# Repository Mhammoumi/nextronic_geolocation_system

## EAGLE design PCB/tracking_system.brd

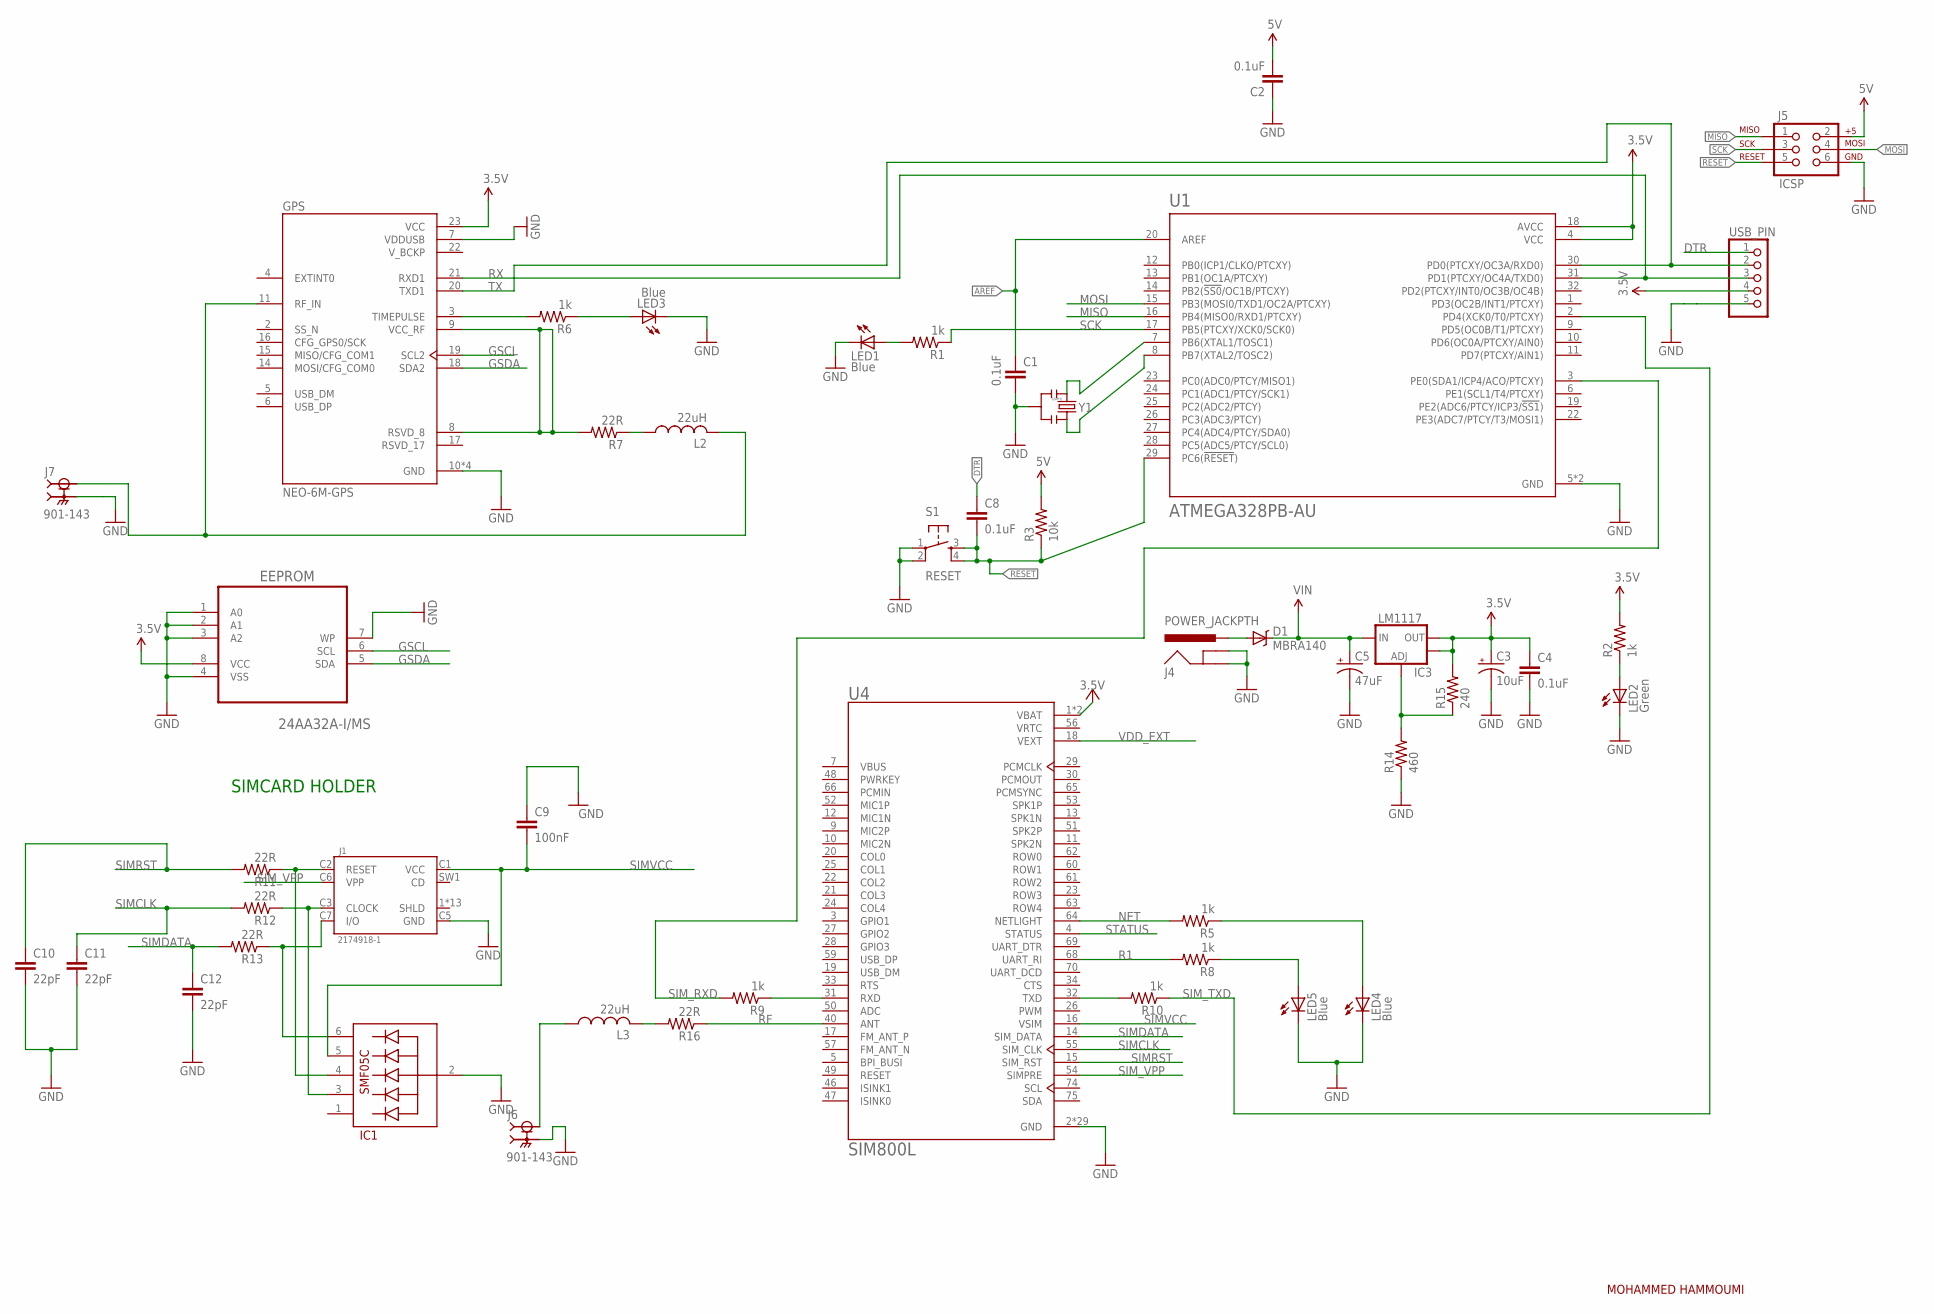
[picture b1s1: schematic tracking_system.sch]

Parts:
C1, C2, C4, C8: 0.1uF; 0603-CAP
C3: 10uF; EIA3216
C5: 47uF; PANASONIC_D; MPN EEE1CA470SP
C9: 100nF; 0603-CAP
C10, C11, C12: 22pF; 0603-CAP
D1: MBRA140; SMA-DIODE; MPN B140-13-F
EEPROM: 24AA32A-I/MS; SOP65P490X110-8N
GPS: NEO-6M-GPS; XCVR_NEO-6M-GPS
IC1: SMF05C; SC-70-6
IC3: LM1117; SOT223-ALT1; MPN LD1117S33TR
J1: 2174918-1; TE_2174918-1
J4: POWER_JACKPTH; POWER_JACK_PTH
J5: ICSP; 2X3
J6, J7: 901-143; AMPHENOL_901-143
L2, L3: 22uH; L3225P
LED1, LED3, LED4, LED5: Blue; LED-1206-NO_SILK
LED2: Green; LED-1206-NO_SILK
R1, R2, R5, R6, R8, R9, R10: 1k; 0603-RES
R3: 10k; 0603-RES
R7, R11, R12, R13, R16: 22R; 0603-RES
R14: 460; 0603-RES
R15: 240; 0603-RES
S1: RESET; TACTILE_SWITCH_SMD
U1: ATMEGA328PB-AU; QFP80P900X900X120-32N
U4: SIM800L; MODULE_SIM800L
USB_PIN: PINHD-1X5; 1X05
Y1: 16MHz; RESONATOR-SMD

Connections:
3.3V: EEPROM.8 (VCC), GPS.23 (VCC)
5V: C2.2, C3.A (+), C4.1, IC3.2 (OUT), IC3.4 (OUT), J5.2, R2.2, R3.2, R15.2, U1.4 (VCC), U1.18 (AVCC), USB_PIN.4
AREF: C1.1, U1.20 (AREF)
DTR: C8.1, USB_PIN.1
GND: C1.2, C2.1, C3.C (-), C4.2, C5.-, C9.1, C10.2, C11.2, C12.2, EEPROM.1 (A0), EEPROM.2 (A1), EEPROM.3 (A2), EEPROM.4 (VSS), EEPROM.7 (WP), GPS.7 (VDDUSB), GPS.10 (GND), GPS.12 (GND), GPS.13 (GND), GPS.24 (GND), IC1.2, J1.C5 (GND), J4.GND, J4.GNDBREAK, J5.6, J6.2, J6.3 (2), J6.4 (2), J6.5 (2), J7.2, J7.3 (2), J7.4 (2), J7.5 (2), LED1.C, LED2.C, LED3.C, LED4.C, LED5.C, R14.1, S1.1, S1.2, U1.5 (GND), U1.21 (GND), U4.2 (GND), U4.6 (GND), U4.8 (GND), U4.35 (GND), U4.37 (GND), U4.38 (GND), U4.39 (GND), U4.41 (GND), U4.43 (GND), U4.44 (GND), U4.45 (GND), U4.58 (GND), U4.67 (GND), U4.71 (GND), U4.72 (GND), U4.73 (GND), U4.76 (GND), U4.77 (GND), U4.78 (GND), U4.79 (GND), U4.80 (GND), U4.81 (GND), U4.82 (GND), U4.83 (GND), U4.84 (GND), U4.85 (GND), U4.86 (GND), U4.87 (GND), U4.88 (GND), USB_PIN.5, Y1.2
GSCL: EEPROM.6 (SCL), GPS.19 (SCL2)
GSDA: EEPROM.5 (SDA), GPS.18 (SDA2)
MISO: J5.1, U1.16 (PB4(MISO0/RXD1/PTCXY))
MOSI: J5.4, U1.15 (PB3(MOSI0/TXD1/OC2A/PTCXY))
unnamed: LED2.A, R2.1
unnamed: LED1.A, R1.2
unnamed: U1.7 (PB6(XTAL1/TOSC1)), Y1.1
unnamed: U1.8 (PB7(XTAL2/TOSC2)), Y1.3
unnamed: D1.A, J4.PWR
unnamed: GPS.3 (TIMEPULSE), R6.2
unnamed: LED3.A, R6.1
unnamed: GPS.8 (RSVD_8), GPS.9 (VCC_RF), R7.2
unnamed: L2.1, R7.1
unnamed: GPS.11 (RF_IN), J7.1, L2.2
unnamed: R9.1, U4.31 (RXD)
unnamed: R10.2, U4.32 (TXD)
unnamed: IC1.6, J1.C7 (I/O), R13.1
unnamed: LED5.A, R8.1
unnamed: IC3.1 (ADJ), R14.2, R15.1
unnamed: LED4.A, R5.1
unnamed: IC1.3, J1.C3 (CLOCK), R12.1
unnamed: IC1.4, J1.C2 (RESET), R11.1
unnamed: L3.2, R16.2
unnamed: J6.1, L3.1
NET: R5.2, U4.64 (NETLIGHT)
R1: R8.2, U4.68 (UART_RI)
RESET: C8.2, J5.5, R3.1, S1.3, S1.4, U1.29 (PC6(!RESET!))
RF: R16.1, U4.40 (ANT)
RX: GPS.21 (RXD1), U1.31 (PD1(PTCXY/OC4A/TXD0)), USB_PIN.3
SCK: J5.3, R1.1, U1.17 (PB5(PTCXY/XCK0/SCK0))
SHLD: J1.1 (SHLD), J1.2 (SHLD), J1.3 (SHLD), J1.4 (SHLD), J1.5 (SHLD), J1.6 (SHLD), J1.7 (SHLD), J1.8 (SHLD), J1.9 (SHLD), J1.10 (SHLD), J1.11 (SHLD), J1.12 (SHLD), J1.13 (SHLD)
SIMCLK: C11.1, R12.2, U4.55 (SIM_CLK)
SIMDATA: C12.1, R13.2, U4.14 (SIM_DATA)
SIMRST: C10.1, R11.2, U4.15 (SIM_RST)
SIMVCC: C9.2, IC1.5, J1.C1 (VCC), U4.16 (VSIM)
SIM_RXD: R9.2, U1.3 (PE0(SDA1/ICP4/ACO/PTCXY))
SIM_TXD: R10.1, U1.2 (PD4(XCK0/T0/PTCXY))
SIM_VPP: J1.C6 (VPP), U4.54 (SIMPRE)
STATUS: U4.4 (STATUS)
TX: GPS.20 (TXD1), U1.30 (PD0(PTCXY/OC3A/RXD0)), USB_PIN.2
VCC: U4.1 (VBAT), U4.42 (VBAT)
VDD_EXT: U4.18 (VEXT)
VIN: C5.+, D1.C, IC3.3 (IN)
VRTC: U4.56 (VRTC)
V_BCKP: GPS.22 (V_BCKP)

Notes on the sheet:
SIMCARD HOLDER
MOHAMMED HAMMOUMI

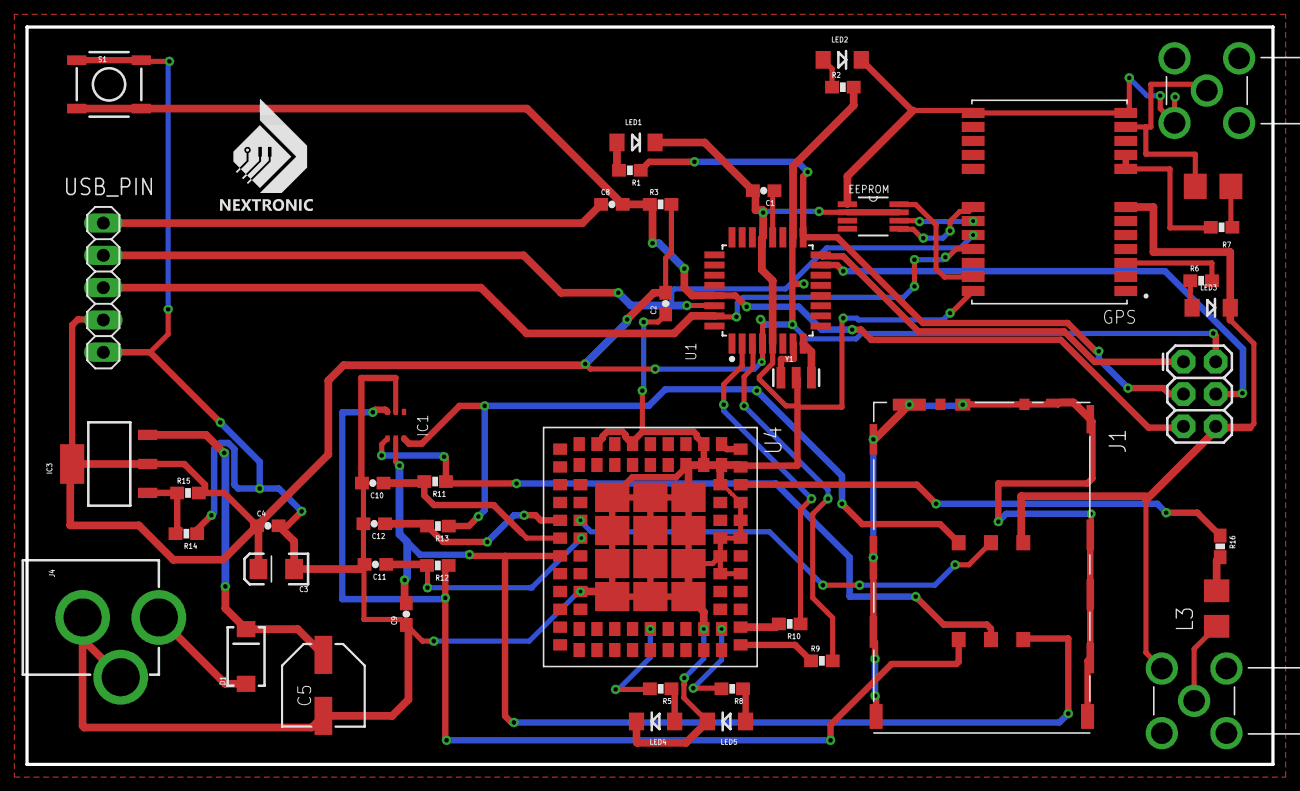
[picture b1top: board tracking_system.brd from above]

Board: 2 copper layers, 98.0 x 58.0 mm, 47 parts (0 on the bottom side), 46 nets.

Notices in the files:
parts and their libraries:
SparkFun-Connectors: Licensing: CC v3.0 Share-Alike You are welcome to use this library for commercial purposes.
